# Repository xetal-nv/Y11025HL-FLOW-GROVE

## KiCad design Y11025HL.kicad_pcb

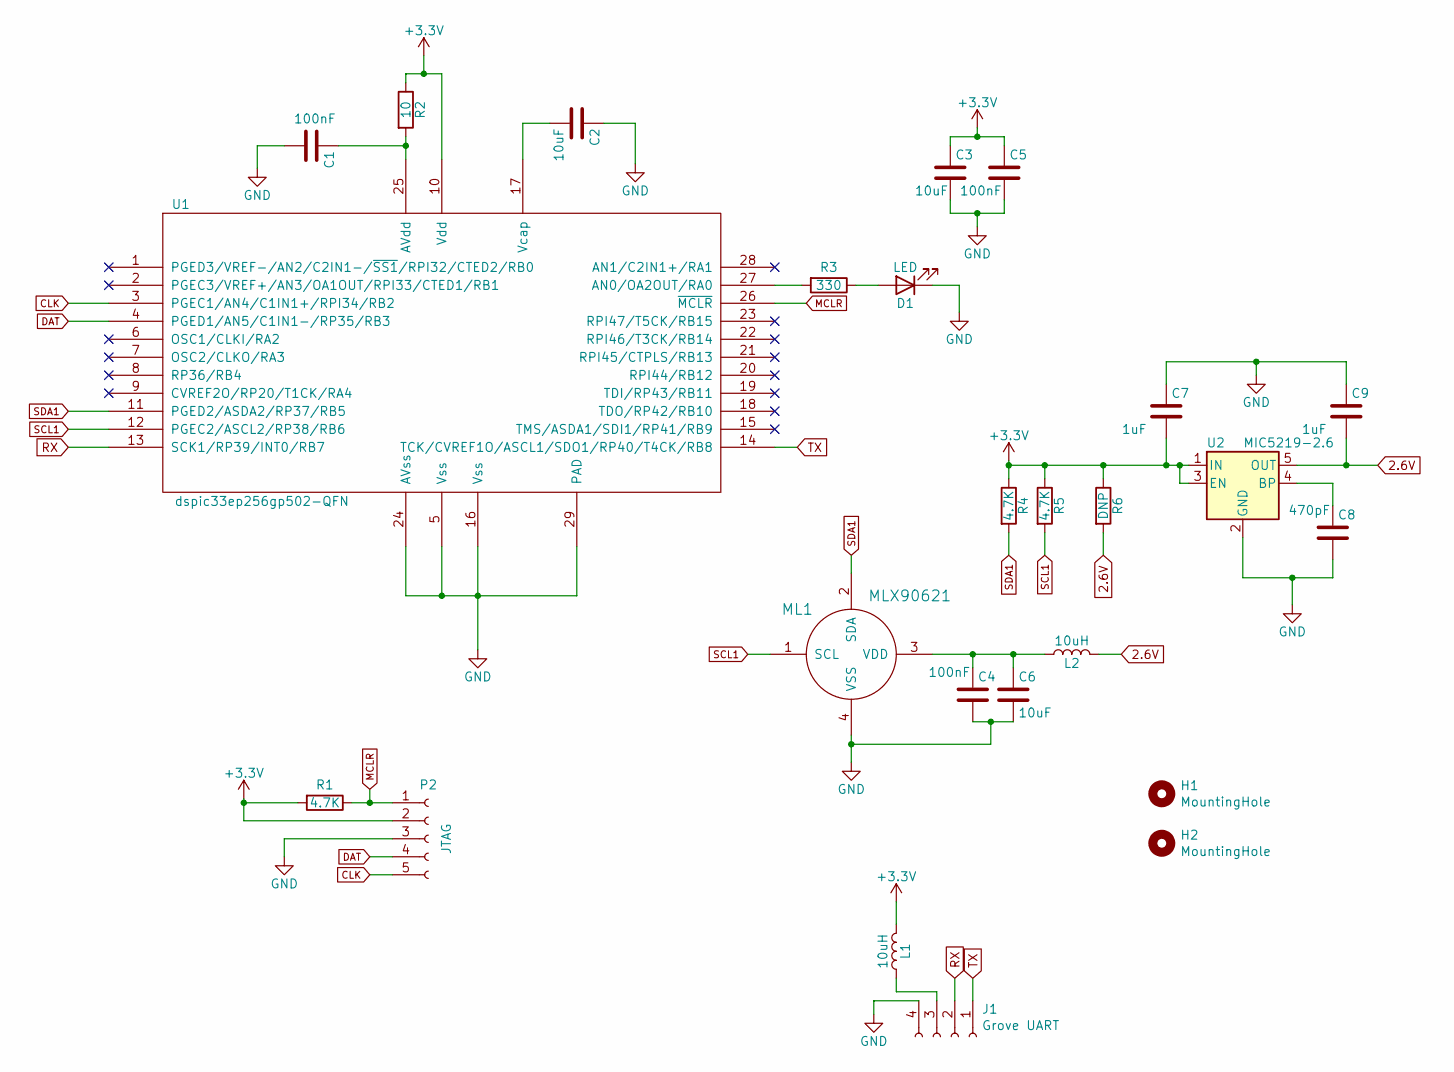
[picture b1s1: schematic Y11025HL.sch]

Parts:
C1, C4, C5: 100nF; C_0402_1005Metric
C2, C3, C6: 10uF; C_0402_1005Metric
C7, C9: 1uF; C_0402_1005Metric
C8: 470pF; C_0402_1005Metric
D1: LED; LED_0402_1005Metric
H1, H2: MountingHole; MountingHole_2.2mm_M2
J1: Grove UART; Grove-4P-SMD
L1, L2: 10uH; L_0603_1608Metric
ML1: MLX90621
P2: JTAG; PinHeader_1x05_P1.27mm_Vertical
R1, R4, R5: 4.7K; R_0402_1005Metric
R2: 10; R_0402_1005Metric
R3: 330; R_0402_1005Metric
R6: DNP; R_0402_1005Metric
U1: dspic33ep256gp502-QFN; QFN-28-1EP_6x6mm_P0.65mm_EP4.25x4.25mm
U2: MIC5219-2.6; SOT-23-5

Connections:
2.6V: C9.2, L2.2, R6.2, U2.5 (OUT)
+3V3: C3.1, C5.1, C7.2, L1.2, P2.2, R1.2, R2.1, R4.1, R5.1, R6.1, U1.10 (Vdd), U2.1 (IN), U2.3 (EN)
CLK: P2.5, U1.3 (PGEC1/AN4/C1IN1+/RPI34/RB2)
DAT: P2.4, U1.4 (PGED1/AN5/C1IN1-/RP35/RB3)
GND: C1.2, C2.1, C3.2, C4.2, C5.2, C6.2, C7.1, C8.2, C9.1, D1.1 (K), J1.4, ML1.4 (VSS), P2.3, U1.5 (Vss), U1.16 (Vss), U1.24 (AVss), U1.29 (PAD), U2.2 (GND)
MCLR: P2.1, R1.1, U1.26 (~MCLR~)
unnamed: C1.1, R2.2, U1.25 (AVdd)
unnamed: C2.2, U1.17 (Vcap)
unnamed: C4.1, C6.1, L2.1, ML1.3 (VDD)
unnamed: C8.1, U2.4 (BP)
unnamed: D1.2 (A), R3.1
unnamed: J1.3, L1.1
unnamed: R3.2, U1.27 (AN0/OA2OUT/RA0)
RX: J1.2, U1.13 (SCK1/RP39/INT0/RB7)
SCL1: ML1.1 (SCL), R5.2, U1.12 (PGEC2/ASCL2/RP38/RB6)
SDA1: ML1.2 (SDA), R4.2, U1.11 (PGED2/ASDA2/RP37/RB5)
TX: J1.1, U1.14 (TCK/CVREF1O/ASCL1/SDO1/RP40/T4CK/RB8)

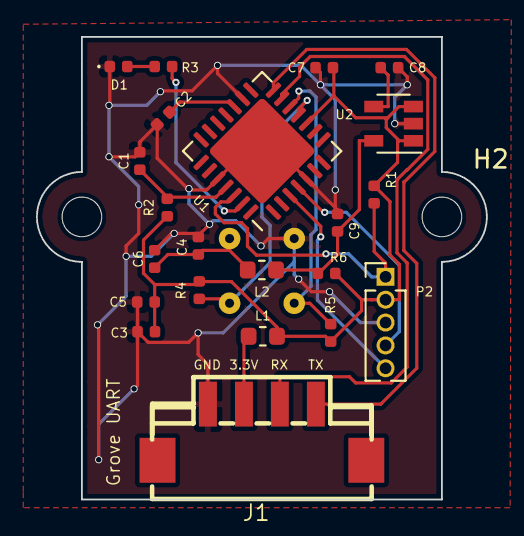
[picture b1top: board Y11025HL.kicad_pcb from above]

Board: 2 copper layers, 25.0 x 25.7 mm, 25 parts (1 on the bottom side), 17 nets.

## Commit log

2021-04-06 cleaned
